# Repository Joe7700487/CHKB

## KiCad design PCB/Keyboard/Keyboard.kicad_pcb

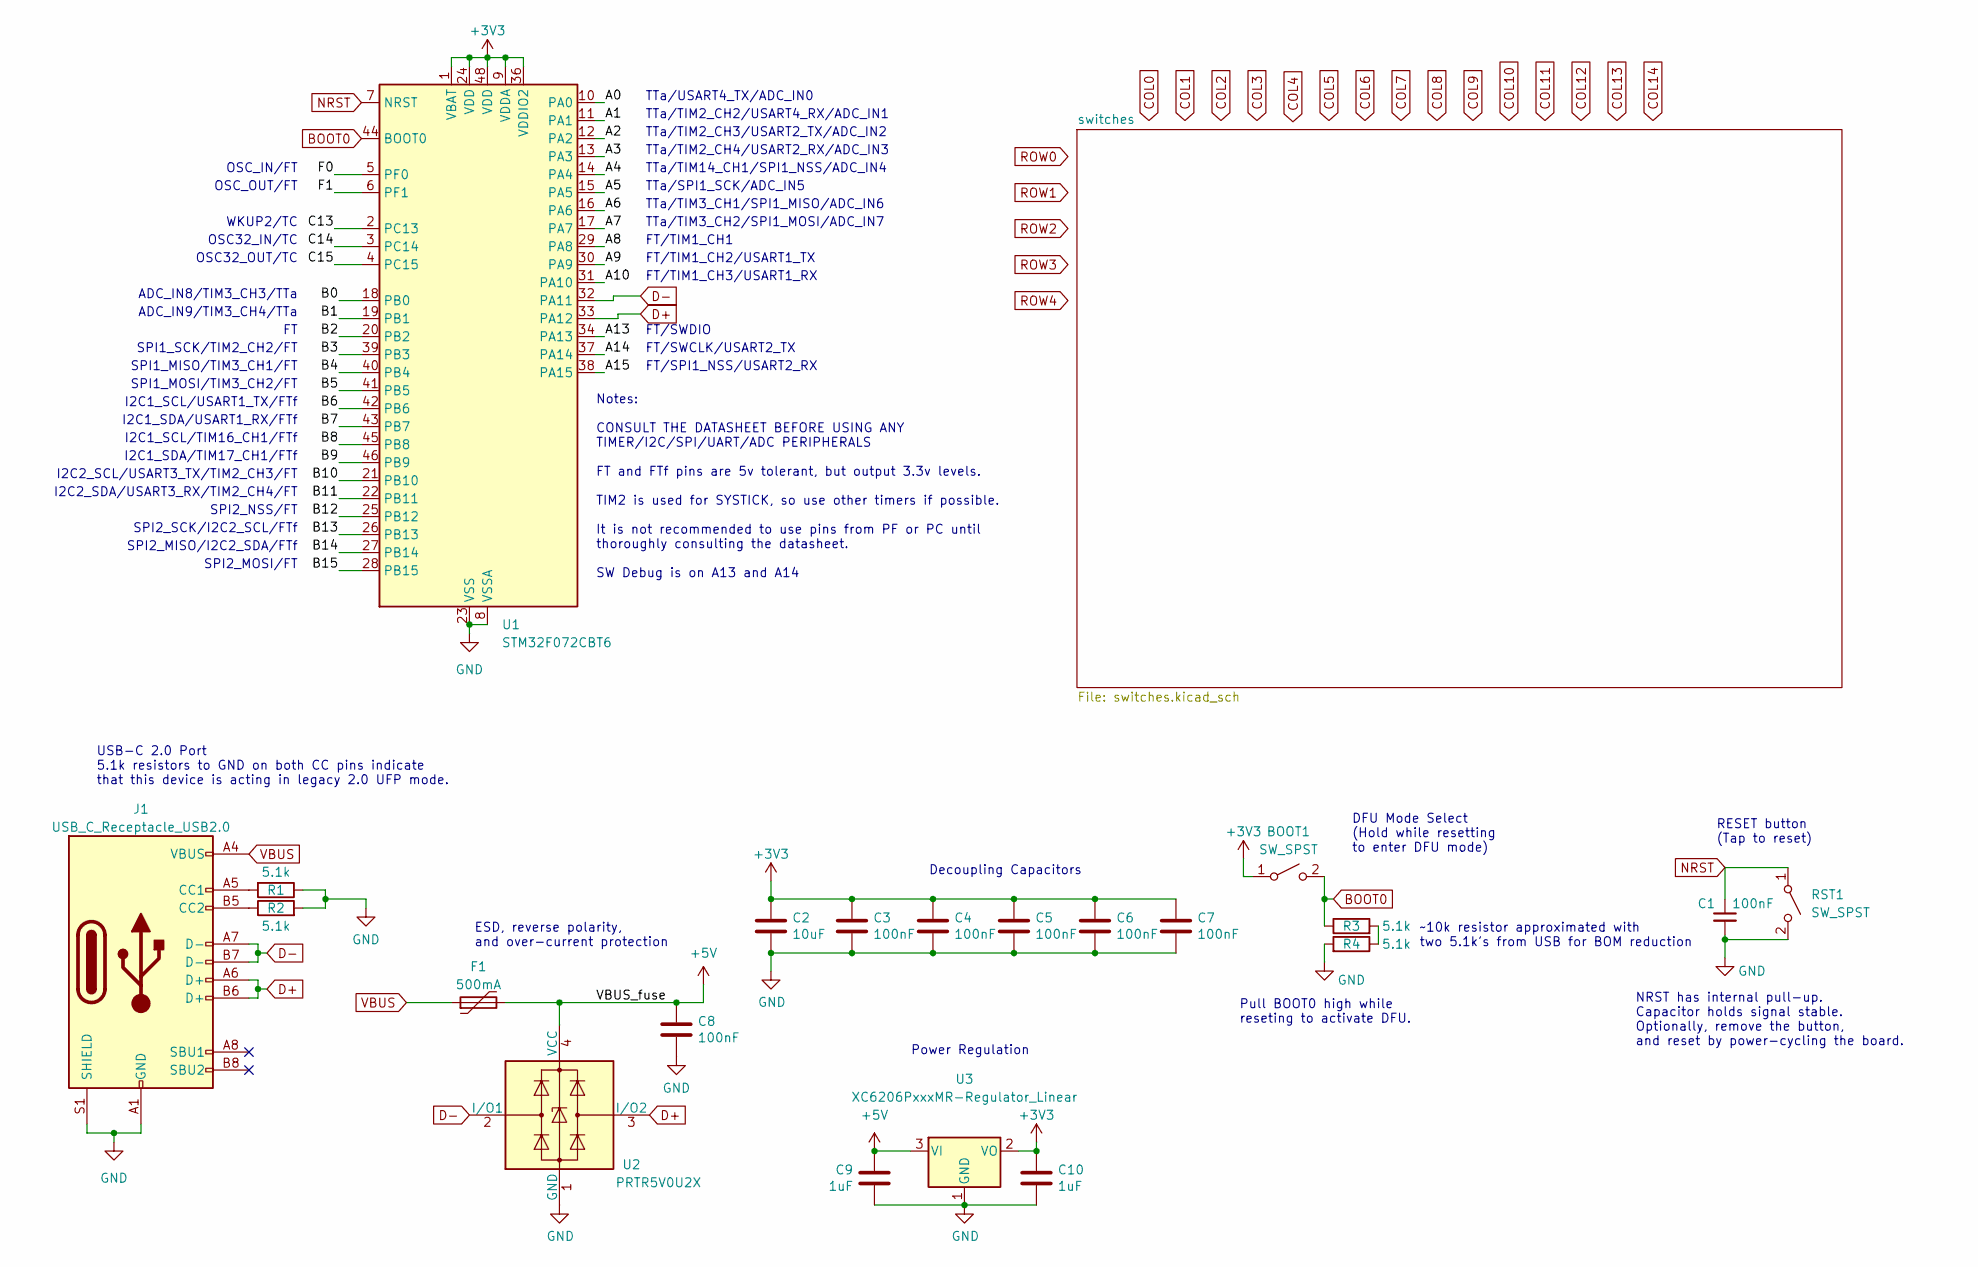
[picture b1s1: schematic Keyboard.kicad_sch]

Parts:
BOOT1: SW_SPST; SW_SPST_TL3342
C1, C3, C4, C5, C6, C7, C8: 100nF; C_0402_1005Metric; LCSC C307331
C2: 10uF; C_0603_1608Metric; LCSC C307331
C9, C10: 1uF; C_0402_1005Metric; LCSC C307331
F1: 500mA; Fuse_1206_3216Metric; LCSC C135341
J1: USB_C_Receptacle_USB2.0; USB_C_Receptacle_HRO_TYPE-C-31-M-12; JlcRotOffset 180
R1, R2, R3, R4: 5.1k; R_0402_1005Metric
RST1: SW_SPST; SW_SPST_TL3342
U1: STM32F072CBT6; LQFP-48_7x7mm_P0.5mm; JlcRotOffset 90
U2: PRTR5V0U2X; SOT-143; LCSC C2827688
U3: XC6206PxxxMR-Regulator_Linear; SOT-23; LCSC C5446

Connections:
+3V3: BOOT1.1 (A), C2.1, C3.1, C4.1, C5.1, C6.1, C7.1, C10.1, U1.1 (VBAT), U1.9 (VDDA), U1.24 (VDD), U1.36 (VDDIO2), U1.48 (VDD), U3.2 (VO)
+5V: C8.1, C9.1, F1.2, U2.4 (VCC), U3.3 (VI)
/A0: U1.10 (PA0)
/A1: U1.11 (PA1)
/A2: U1.12 (PA2)
/A3: U1.13 (PA3)
/A4: U1.14 (PA4)
/A5: U1.15 (PA5)
/A6: U1.16 (PA6)
/A7: U1.17 (PA7)
/A8: U1.29 (PA8)
/A9: U1.30 (PA9)
/A10: U1.31 (PA10)
/A13: U1.34 (PA13)
/A14: U1.37 (PA14)
/A15: U1.38 (PA15)
/B0: U1.18 (PB0)
/B1: U1.19 (PB1)
/B2: U1.20 (PB2)
/B3: U1.39 (PB3)
/B4: U1.40 (PB4)
/B5: U1.41 (PB5)
/B6: U1.42 (PB6)
/B7: U1.43 (PB7)
/B8: U1.45 (PB8)
/B9: U1.46 (PB9)
/B10: U1.21 (PB10)
/B11: U1.22 (PB11)
/B12: U1.25 (PB12)
/B13: U1.26 (PB13)
/B14: U1.27 (PB14)
/B15: U1.28 (PB15)
/C13: U1.2 (PC13)
/C14: U1.3 (PC14)
/C15: U1.4 (PC15)
/F0: U1.5 (PF0)
/F1: U1.6 (PF1)
BOOT0: BOOT1.2 (B), R3.1, U1.44 (BOOT0)
D+: J1.A6 (D+), J1.B6 (D+), U1.33 (PA12), U2.3 (I/O2)
D-: J1.A7 (D-), J1.B7 (D-), U1.32 (PA11), U2.2 (I/O1)
GND: C1.2, C2.2, C3.2, C4.2, C5.2, C6.2, C7.2, C8.2, C9.2, C10.2, J1.A1 (GND), J1.A12 (GND), J1.B1 (GND), J1.B12 (GND), J1.S1 (SHIELD), R1.1, R2.2, R4.2, RST1.2 (B), U1.8 (VSSA), U1.23 (VSS), U1.35 (VSS), U1.47 (VSS), U2.1 (GND), U3.1 (GND)
NRST: C1.1, RST1.1 (A), U1.7 (NRST)
unnamed: J1.A5 (CC1), R1.2
unnamed: J1.B5 (CC2), R2.1
unnamed: R3.2, R4.1
VBUS: F1.1, J1.A4 (VBUS), J1.A9 (VBUS), J1.B4 (VBUS), J1.B9 (VBUS)

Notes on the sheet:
SPI1_SCK/TIM2_CH2/FT
FT/TIM1_CH1
FT/TIM1_CH3/USART1_RX
SPI2_NSS/FT
Notes: CONSULT THE DATASHEET BEFORE USING ANY TIMER/I2C/SPI/UART/ADC PERIPHERALS FT and FTf pins are 5v tolerant, but output 3.3v levels. TIM2 is used for SYSTICK, so use other timers if possible. It is not recommended to use pins from PF or PC until thoroughly consulting the datasheet. SW Debug is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
TTa/TIM2_CH4/USART2_RX/ADC_IN3
NRST has internal pull-up. Capacitor holds signal stable. Optionally, remove the button, and reset by power-cycling the board.
FT/SWDIO
Decoupling Capacitors
SPI1_MOSI/TIM3_CH2/FT
ADC_IN9/TIM3_CH4/TTa
I2C2_SCL/USART3_TX/TIM2_CH3/FT
SPI2_MISO/I2C2_SDA/FTf
FT/SWCLK/USART2_TX
I2C1_SCL/TIM16_CH1/FTf
~10k resistor approximated with two 5.1k's from USB for BOM reduction
TTa/TIM2_CH2/USART4_RX/ADC_IN1
USB-C 2.0 Port 5.1k resistors to GND on both CC pins indicate that this device is acting in legacy 2.0 UFP mode.
TTa/TIM2_CH3/USART2_TX/ADC_IN2
OSC_IN/FT
DFU Mode Select (Hold while resetting to enter DFU mode)
WKUP2/TC
I2C2_SDA/USART3_RX/TIM2_CH4/FT
ADC_IN8/TIM3_CH3/TTa
RESET button (Tap to reset)
Pull BOOT0 high while reseting to activate DFU.
I2C1_SDA/TIM17_CH1/FTf
TTa/SPI1_SCK/ADC_IN5
TTa/TIM3_CH1/SPI1_MISO/ADC_IN6
TTa/TIM3_CH2/SPI1_MOSI/ADC_IN7
OSC32_OUT/TC
FT/SPI1_NSS/USART2_RX
SPI1_MISO/TIM3_CH1/FT
OSC32_IN/TC
TTa/TIM14_CH1/SPI1_NSS/ADC_IN4
I2C1_SDA/USART1_RX/FTf
SPI2_MOSI/FT
FT/TIM1_CH2/USART1_TX
Power Regulation
SPI2_SCK/I2C2_SCL/FTf

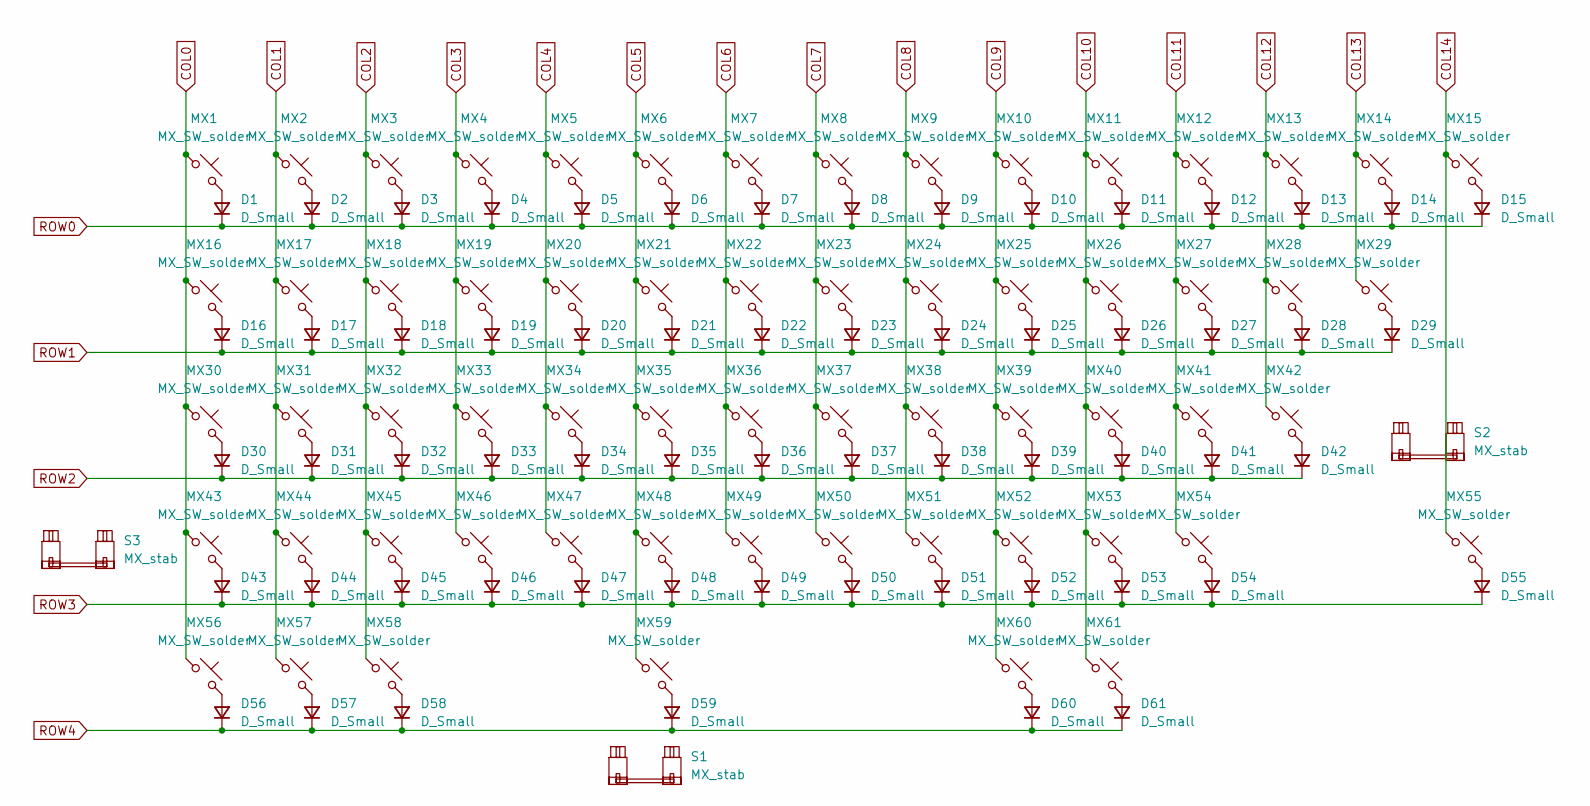
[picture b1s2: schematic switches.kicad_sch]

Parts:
D1, D2, D3, D4, D5, D6, D7, D8, D9, D10, D11, D12, D13, D14, D15, D16, D17, D18, D19, D20, D21, D22, D23, D24, D25, D26, D27, D28, D29, D30, D31, D32, D33, D34, D35, D36, D37, D38, D39, D40, D41, D42, D43, D44, D45, D46, D47, D48, D49, D50, D51, D52, D53, D54, D55, D56, D57, D58, D59, D60, D61: D_Small; D_SOD-123
MX1, MX2, MX3, MX4, MX5, MX6, MX7, MX8, MX9, MX10, MX11, MX12, MX13, MX14, MX15, MX16, MX17, MX18, MX19, MX20, MX21, MX22, MX23, MX24, MX25, MX26, MX27, MX28, MX29, MX30, MX31, MX32, MX33, MX34, MX35, MX36, MX37, MX38, MX39, MX40, MX41, MX42, MX43, MX44, MX45, MX46, MX47, MX48, MX49, MX50, MX51, MX52, MX53, MX54, MX55, MX56, MX57, MX58, MX59, MX60, MX61: MX_SW_solder; SW_MX_1u
S1: MX_stab; STAB_MX_6u
S2, S3: MX_stab; STAB_MX_2.25u

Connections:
COL0: MX1.1, MX16.1, MX30.1, MX43.1, MX56.1
COL1: MX2.1, MX17.1, MX31.1, MX44.1, MX57.1
COL2: MX3.1, MX18.1, MX32.1, MX45.1, MX58.1
COL3: MX4.1, MX19.1, MX33.1, MX46.1
COL4: MX5.1, MX20.1, MX34.1, MX47.1
COL5: MX6.1, MX21.1, MX35.1, MX48.1, MX59.1
COL6: MX7.1, MX22.1, MX36.1, MX49.1
COL7: MX8.1, MX23.1, MX37.1, MX50.1
COL8: MX9.1, MX24.1, MX38.1, MX51.1
COL9: MX10.1, MX25.1, MX39.1, MX52.1, MX60.1
COL10: MX11.1, MX26.1, MX40.1, MX53.1, MX61.1
COL11: MX12.1, MX27.1, MX41.1, MX54.1
COL12: MX13.1, MX28.1, MX42.1
COL13: MX14.1, MX29.1
COL14: MX15.1, MX55.1
unnamed: D1.2 (A), MX1.2
unnamed: D2.2 (A), MX2.2
unnamed: D3.2 (A), MX3.2
unnamed: D4.2 (A), MX4.2
unnamed: D5.2 (A), MX5.2
unnamed: D6.2 (A), MX6.2
unnamed: D7.2 (A), MX7.2
unnamed: D8.2 (A), MX8.2
unnamed: D9.2 (A), MX9.2
unnamed: D10.2 (A), MX10.2
unnamed: D11.2 (A), MX11.2
unnamed: D12.2 (A), MX12.2
unnamed: D13.2 (A), MX13.2
unnamed: D14.2 (A), MX14.2
unnamed: D15.2 (A), MX15.2
unnamed: D16.2 (A), MX16.2
unnamed: D17.2 (A), MX17.2
unnamed: D18.2 (A), MX18.2
unnamed: D19.2 (A), MX19.2
unnamed: D20.2 (A), MX20.2
unnamed: D21.2 (A), MX21.2
unnamed: D22.2 (A), MX22.2
unnamed: D23.2 (A), MX23.2
unnamed: D24.2 (A), MX24.2
unnamed: D25.2 (A), MX25.2
unnamed: D26.2 (A), MX26.2
unnamed: D27.2 (A), MX27.2
unnamed: D28.2 (A), MX28.2
unnamed: D29.2 (A), MX29.2
unnamed: D30.2 (A), MX30.2
unnamed: D31.2 (A), MX31.2
unnamed: D32.2 (A), MX32.2
unnamed: D33.2 (A), MX33.2
unnamed: D34.2 (A), MX34.2
unnamed: D35.2 (A), MX35.2
unnamed: D36.2 (A), MX36.2
unnamed: D37.2 (A), MX37.2
unnamed: D38.2 (A), MX38.2
unnamed: D39.2 (A), MX39.2
unnamed: D40.2 (A), MX40.2
unnamed: D41.2 (A), MX41.2
unnamed: D42.2 (A), MX42.2
unnamed: D43.2 (A), MX43.2
unnamed: D44.2 (A), MX44.2
unnamed: D45.2 (A), MX45.2
unnamed: D46.2 (A), MX46.2
unnamed: D47.2 (A), MX47.2
unnamed: D48.2 (A), MX48.2
unnamed: D49.2 (A), MX49.2
unnamed: D50.2 (A), MX50.2
unnamed: D51.2 (A), MX51.2
unnamed: D52.2 (A), MX52.2
unnamed: D53.2 (A), MX53.2
unnamed: D54.2 (A), MX54.2
unnamed: D55.2 (A), MX55.2
unnamed: D56.2 (A), MX56.2
unnamed: D57.2 (A), MX57.2
unnamed: D58.2 (A), MX58.2
unnamed: D59.2 (A), MX59.2
unnamed: D60.2 (A), MX60.2
unnamed: D61.2 (A), MX61.2
ROW0: D1.1 (K), D2.1 (K), D3.1 (K), D4.1 (K), D5.1 (K), D6.1 (K), D7.1 (K), D8.1 (K), D9.1 (K), D10.1 (K), D11.1 (K), D12.1 (K), D13.1 (K), D14.1 (K), D15.1 (K)
ROW1: D16.1 (K), D17.1 (K), D18.1 (K), D19.1 (K), D20.1 (K), D21.1 (K), D22.1 (K), D23.1 (K), D24.1 (K), D25.1 (K), D26.1 (K), D27.1 (K), D28.1 (K), D29.1 (K)
ROW2: D30.1 (K), D31.1 (K), D32.1 (K), D33.1 (K), D34.1 (K), D35.1 (K), D36.1 (K), D37.1 (K), D38.1 (K), D39.1 (K), D40.1 (K), D41.1 (K), D42.1 (K)
ROW3: D43.1 (K), D44.1 (K), D45.1 (K), D46.1 (K), D47.1 (K), D48.1 (K), D49.1 (K), D50.1 (K), D51.1 (K), D52.1 (K), D53.1 (K), D54.1 (K), D55.1 (K)
ROW4: D56.1 (K), D57.1 (K), D58.1 (K), D59.1 (K), D60.1 (K), D61.1 (K)

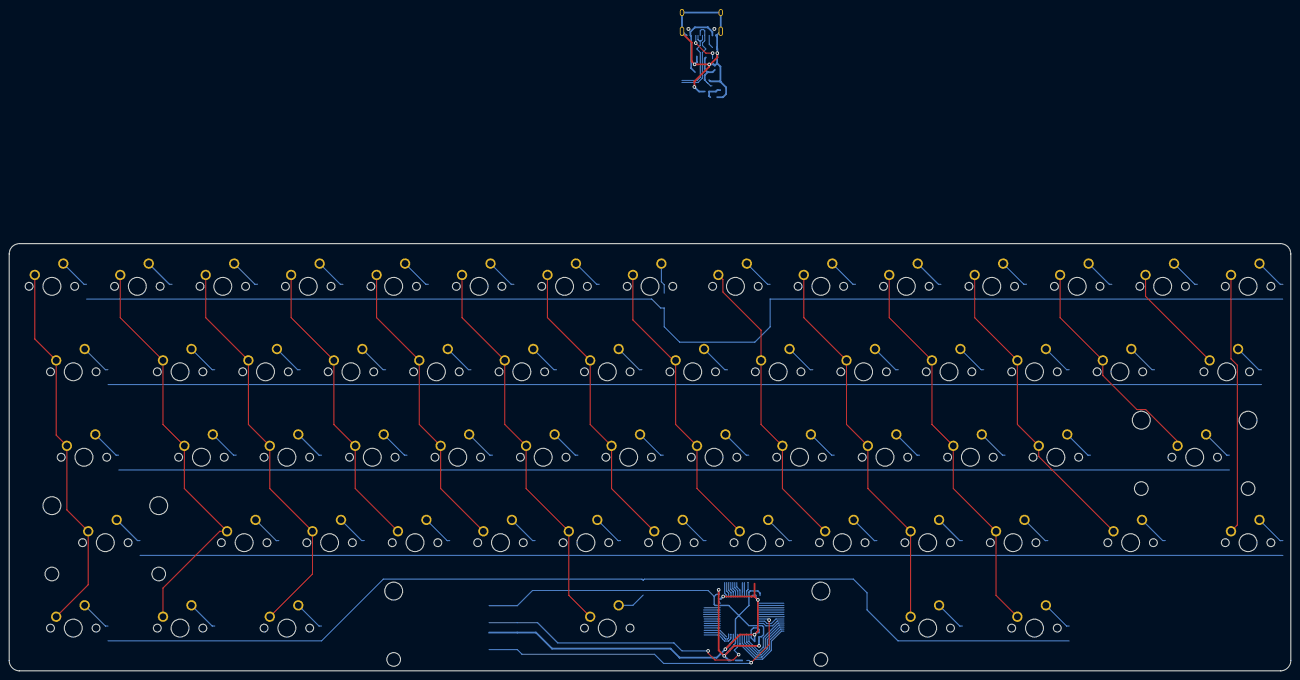
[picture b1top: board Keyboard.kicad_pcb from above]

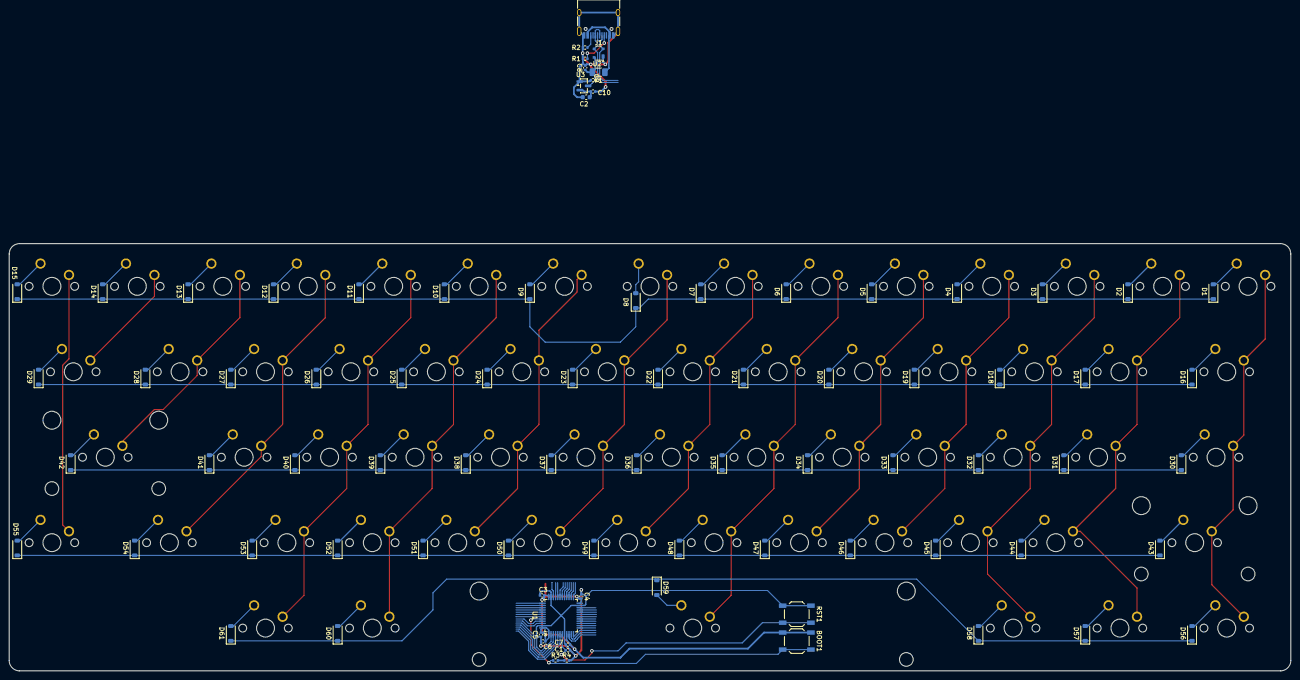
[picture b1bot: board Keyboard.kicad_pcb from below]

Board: 2 copper layers, 285.8 x 95.2 mm, 146 parts (82 on the bottom side), 92 nets.

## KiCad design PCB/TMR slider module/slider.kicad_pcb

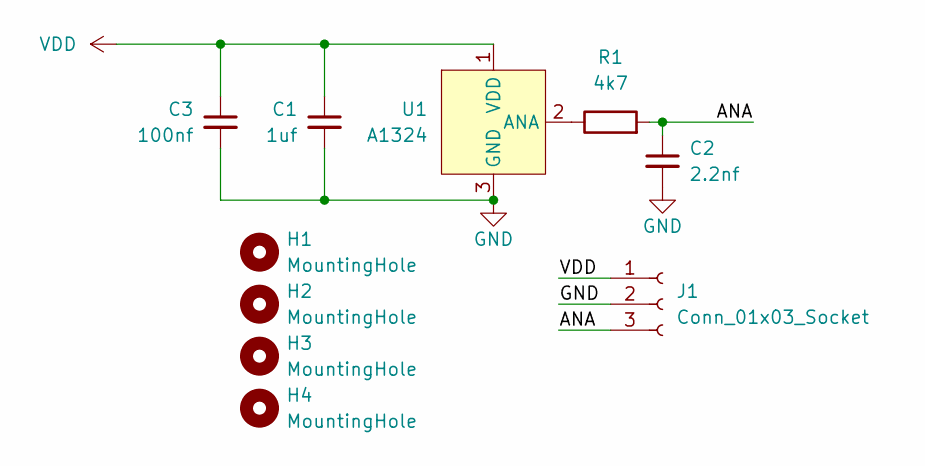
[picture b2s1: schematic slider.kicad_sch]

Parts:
C1: 1uf; C_0805_2012Metric
C2: 2.2nf; C_0805_2012Metric
C3: 100nf; C_0805_2012Metric
H1, H2, H3, H4: MountingHole; MountingHole_2.2mm_M2
J1: Conn_01x03_Socket; PinHeader_1x03_P2.54mm_Vertical
R1: 4k7; R_0805_2012Metric
U1: A1324; SOT-23W

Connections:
/ANA: C2.1, J1.3, R1.2
GND: C1.2, C2.2, C3.2, J1.2, U1.3 (GND)
unnamed: R1.1, U1.2 (ANA)
VDD: C1.1, C3.1, J1.1, U1.1 (VDD)

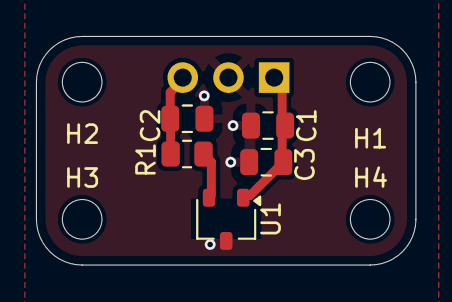
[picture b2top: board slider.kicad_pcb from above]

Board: 2 copper layers, 21.1 x 12.7 mm, 10 parts (1 on the bottom side), 4 nets.

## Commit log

2026-03-15 Init
2026-03-15 add keyboard pcb
2026-03-16 wire rows and cols
2026-03-16 fix footprints
2026-03-19 Finalize slider PCB
2026-03-21 organize stm32
2026-03-22 wire stm32
